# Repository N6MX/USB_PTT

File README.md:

#======================================================================================
#======================================================================================
# USB_PTT
# This is the design for a USB Push-To-Talk interface for amateur radio.
# This design was intended with work with the Yaesu FT-8900R, but will also work on radios with a similar interface.
#
# Author: Dylon Mutz, KK6OTK
# Email : dylon.mutz@gmail.com
#
# 10/7/2017 -- Initial release
#======================================================================================
#======================================================================================

99-usb_ptt.rules
   A udev rule is needed to set the device file to the dialout group with read/write permissions.
   Add this rules file to /etc/udev/rules.d/

ptt_driver/ptt_driver.ko
   This is the Linux kernel module (or driver) that is compiled from ptt_driver.c. This is the system-level middleman between the userspace application and the actual USB device hardware.
   The module can be loaded manually running the command "insmod <path to ptt_driver.ko"
   To allow the module to load automatically when the system is booted, follow the next steps:
      1) Make a new module directory in the kernel module folder
            "mkdir /lib/modules/`uname -r`/kernel/driver/ptt_driver"
      2) Allow the modprobe command to find the module by placing it under the "/lib/modules/`uname -r`" directory
            "cp usb_ptt/ptt_driver.ko /lib/modules/`uname -r`/kernel/driver/ptt_driver/"
      3) Regenerate module dependencies
            "depmod -ae
      4) Allow module to automatically load by placing a module config file in the "/etc/modules-load.d" directory
            "cp ptt_driver.conf /etc/modules-load.d/"

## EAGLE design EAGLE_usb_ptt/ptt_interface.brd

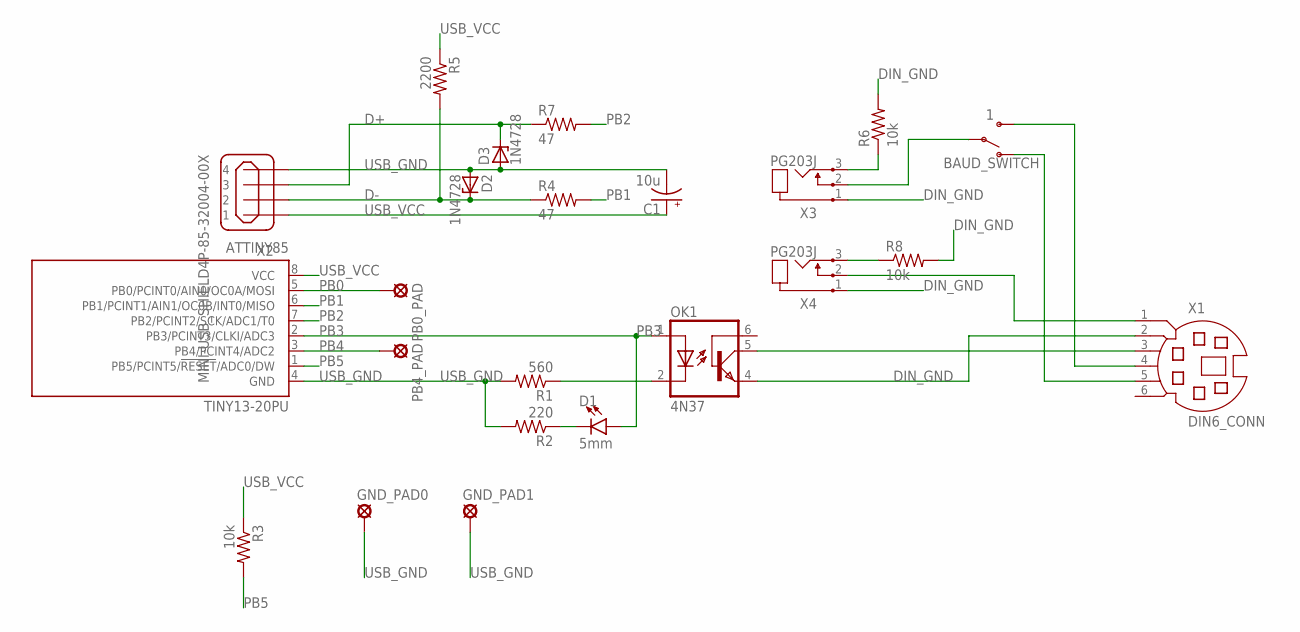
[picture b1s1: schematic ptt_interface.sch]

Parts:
ATTINY85: TINY13-20PU; DIL08
BAUD_SWITCH: 1; SWITCH_SPDT_PTH_15X5.6MM
C1: 10u; E2,5-5
D1: 5mm; LED_5MM
D2, D3: 1N4728; DO41Z10
GND_PAD0, GND_PAD1: LSP11
OK1: 4N37; DIL06
PB0_PAD, PB4_PAD: LSP11
R1: 560; 0207/10
R2: 220; 0207/10
R3, R6, R8: 10k; 0207/10
R4, R7: 47; 0207/10
R5: 2200; 0207/10
X1: DIN6_CONN; MDIN06SS
X2: MINI-USB_SHIELD4P-85-32004-00X; 85-32004-00X
X3, X4: PG203J

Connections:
D+: D3.C, R7.1, X2.3
D-: D2.C, R4.1, R5.2, X2.2
DIN_GND: OK1.4 (EMI), R6.2, R8.2, X1.2, X3.1, X4.1
unnamed: OK1.2 (C), R1.1
unnamed: D1.K (C), R2.1
unnamed: OK1.5 (COL), X1.3
unnamed: BAUD_SWITCH.2, X3.2 (3)
unnamed: R6.1, X3.3 (2)
unnamed: R8.1, X4.3 (2)
unnamed: BAUD_SWITCH.3 (S), X1.4
unnamed: BAUD_SWITCH.1 (O), X1.5
unnamed: X1.1, X4.2 (3)
PB0: ATTINY85.5 (PB0/PCINT0/AIN0/OC0A/MOSI), PB0_PAD.MP
PB1: ATTINY85.6 (PB1/PCINT1/AIN1/OC0B/INT0/MISO), R4.2
PB2: ATTINY85.7 (PB2/PCINT2/SCK/ADC1/T0), R7.2
PB3: ATTINY85.2 (PB3/PCINT3/CLKI/ADC3), D1.A, OK1.1 (A)
PB4: ATTINY85.3 (PB4/PCINT4/ADC2), PB4_PAD.MP
PB5: ATTINY85.1 (PB5/PCINT5/!RESET!/ADC0/DW), R3.2
USB_GND: ATTINY85.4 (GND), C1.-, D2.A, D3.A, GND_PAD0.MP, GND_PAD1.MP, R1.2, R2.2, X2.4
USB_VCC: ATTINY85.8 (VCC), C1.+, R3.1, R5.1, X2.1

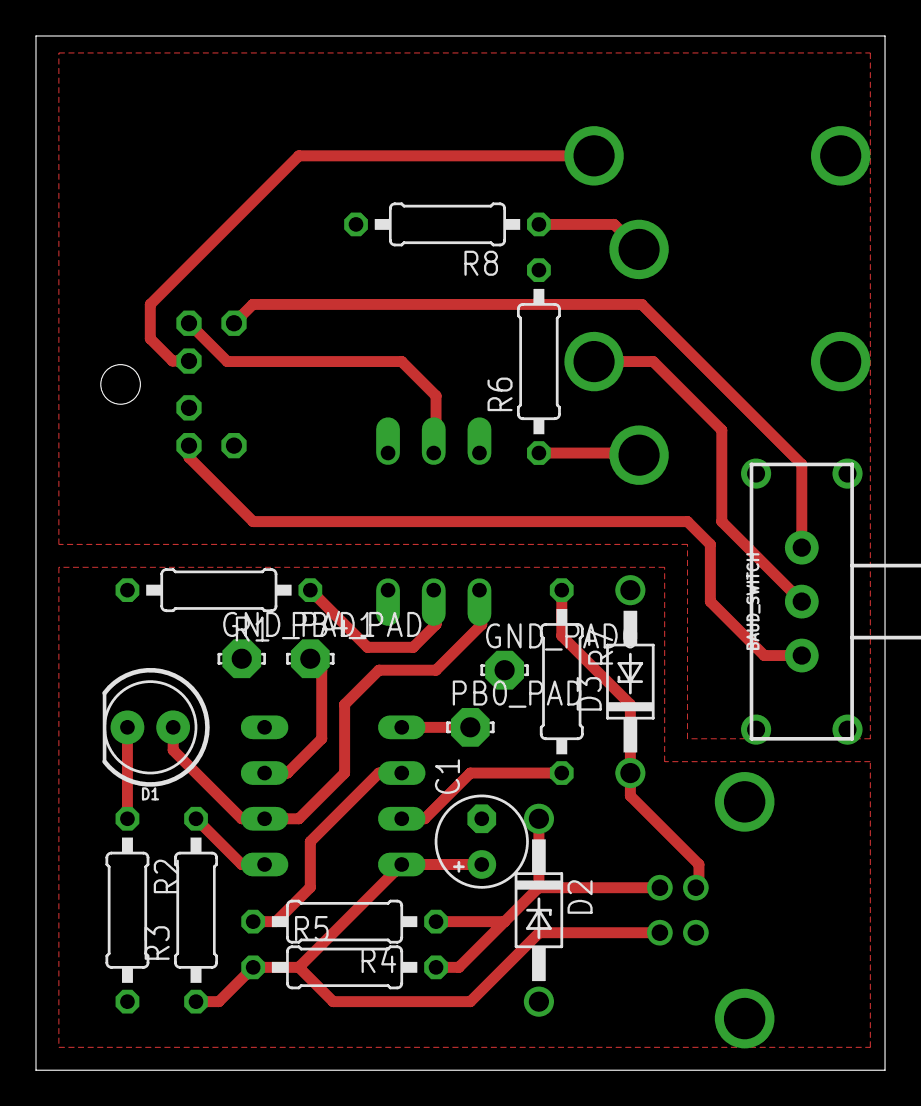
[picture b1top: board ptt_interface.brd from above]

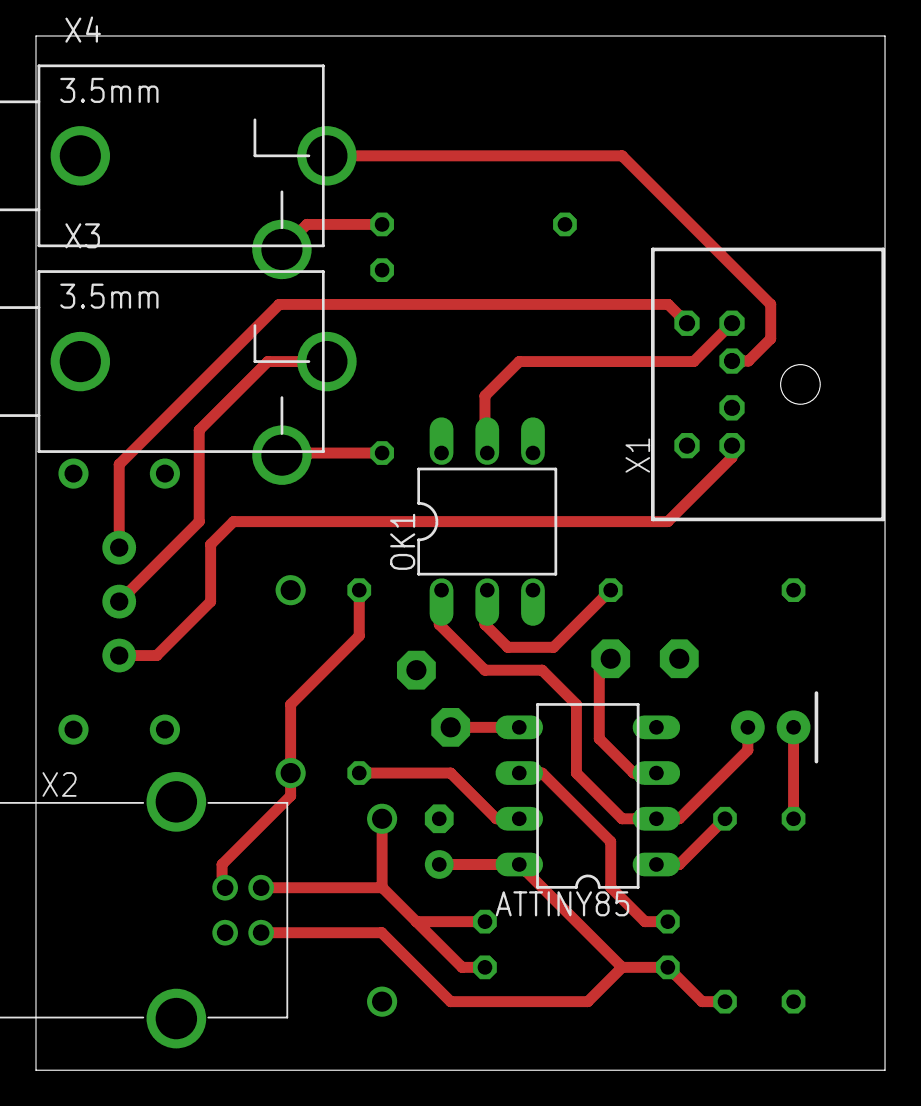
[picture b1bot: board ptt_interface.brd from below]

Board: 2 copper layers, 47.2 x 57.5 mm, 23 parts (6 on the bottom side), 20 nets.

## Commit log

2017-10-08 Initialize repository
2017-10-10 Populate repository with project as-is

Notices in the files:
parts and their libraries:
SparkFun-LED: Licensing: Creative Commons ShareAlike 4.0 International - https://creativecommons.org/licenses/by-sa/4.0
